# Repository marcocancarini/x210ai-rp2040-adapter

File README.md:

# X210Ai RP2040 adapter (rev 2.2)

> ⚠️ **Progetto interrotto**: lo sviluppo di questa scheda adattatore è stato sospeso perché le
> modifiche fatte via patch al firmware dell'EC (IT5571) hanno reso superfluo l'RP2040 esterno.
> Il reverse engineering dell'EC e le relative patch sono nella repo pubblica
> **[marcocancarini/x210ai-ec](https://github.com/marcocancarini/x210ai-ec)**
> (firmware EC patchato in [`firmware/patched/`](https://github.com/marcocancarini/x210ai-ec/tree/main/firmware/patched),
> strumento di patch in [`tools/patch_keyboard.py`](https://github.com/marcocancarini/x210ai-ec/blob/main/tools/patch_keyboard.py)).

Controller USB con RP2040 per la tastiera del ThinkPad X210Ai (ISO italiana e JIS giapponese), su due schede:
**Board A** (RP2040, sotto il palmrest) e **Board B** (flessibile a scalino sul connettore tastiera BTB_R_CONN1),
collegate da un cavo eDP 40 pin. Dettagli in [`passaggio.md`](passaggio.md) e
[`doc/REPORT_rev2.2.md`](doc/REPORT_rev2.2.md).

## Render
Tutti i PNG in [`render/`](render/): viste 2D dei layer a 40 px/mm (`gen2/render.py`) e render 3D
(`kicad-cli pcb render`, 1600×900).

### Board A (28,9 × 16,4 mm)

| 3D top | 3D bottom |
|---|---|
|  |  |
|  |  |

### Board B (29,1 × 28,8 mm)

| 3D top | 3D bottom |
|---|---|
|  |  |
|  |  |

## Checklist

Aggiornata al 28/10/2026 (versione `v2.2.0-rc1`). "Fatto" = verificato sul progetto, non su una scheda costruita.

### Fatto

**Progetto**
- [x] Architettura a due schede + cavo eDP (rev 2.2)
- [x] Modello dati separato: `gen2/design_boardA.py`, `gen2/design_boardB.py`, `gen2/edp_pinout.py`; script di `gen2/` con `--board A|B`
- [x] Firmware (hektopuss `970379d`) invariato: GPIO della Board A coincidenti con `x210ai_pins.h`, `fw3/out/*.uf2` valido
- [x] Emulazione firmware: 14/14 prove, 94/94 tasti (`emu2/`); simulazioni SPICE dei MOSFET EC e del TrackPoint (`spice2/`)
- [x] Impronte: `JAE_AA01B-S040VA1_T61` (44/44 piazzole come il Gerber T61; variante `_GND41` con le linguette a pin 41), `JAE_AA01B-P040_MB_Plug_Bottom`, `IPEX_20455-040E_90deg`
- [x] Specifica del cavo: [`doc/CABLE_SPEC.md`](doc/CABLE_SPEC.md)
- [x] Ambiente locale (Linux): KiCad 10.0.7, `.venv/` con shapely/gerbonara/cairosvg, Freerouting 1.9.0 + Java 21, ngspice 47, arduino-cli + arduino-pico 6.3.0, `emu2/node_modules`

**Schede**
- [x] Board B a L rovesciata a sandwich (39,7 × 15,4 mm): scartata, sopra la spina della tastiera non c'è spazio (non entra nemmeno una moneta da 5 centesimi, 1,67 mm)
- [x] Board B **a scalino** (29,1 × 28,8 mm): gradino alto con la spina J2 su BTB_R_CONN1, J4 verso il palmrest e Q2/Q3/R13/R14 sotto; scalino flessibile di 1,5 mm; gradino basso sulla scheda madre con il ricettacolo J1 della tastiera a 25° in senso orario. Ingombri dalla cornice di misura fotografata (`gen2/gen_dima_scala.py`), quadrato bianco come zona vietata; dima `doc/x210ai_dima_boardB_scalino_1a1.pdf` provata il 28/10/2026, legenda di tutti i componenti `doc/x210ai_dima_boardB_scalino_legenda.pdf`
- [x] Board B: PCB flessibile **4 strati** (poliimmide ~0,25 mm, In1 GND, via 0,4/0,2; a 2 strati le 30 linee J1 → J4 non si sbrogliano), irrigidimenti su User.1 (FR4 0,2 sopra J2 e sotto J4, poliimmide 0,1 sotto J1), zona di piega senza via. Uscite di J1 (ruotato di 25°) pre-instradate fino al gradino alto, poi Freerouting: ERC = 0, DRC = 0, 0 non connessi, schema = PCB; DFM: rame-bordo 0,25, ponte di maschera 0,2
- [x] Board A compattata a 28,9 × 16,4 mm (era 40 × 25): J4 sotto U1, TrackPoint in due colonne, via +3V3 dedicato per U1.48/49; dima provata sulla scheda madre il 28/10/2026
- [x] Sbroglio Freerouting di entrambe le schede (`-mp 100`): ERC = 0, DRC = 0, 0 non connessi, schema = PCB (`out_boardA/`, `out_boardB/`)
- [x] Isolamento foro-rame 0,2 mm rispettato alzando l'isolamento nel DSN (0,13 mm sulla Board B, 0,10 sulla Board A)
- [x] Controllo DFM: via 0,4/0,2 (A) e 0,3/0,15 (B, anello 0,075), pista minima 0,1, rame-bordo 0,25, ponte di maschera 0,2, via tutte coperte
- [x] KiCad 10: simboli nella libreria di progetto `x210ai.kicad_sym` + `sym-lib-table`, MOSFET da `Transistor_FET`, campi BOM nascosti in serigrafia, testo speculare sul lato B

**Produzione**
- [x] Produttore: JLCPCB per entrambe le schede (Board A rigida 4 strati 0,8 mm; Board B flessibile 4 strati con irrigidimenti)
- [x] Gerber, forature, BOM e CPL (un lato / due lati) per le due schede (`produzione/boardA/`, `produzione/boardB/`); controllo Gerber superato
- [x] Ricettacolo eDP C5160883 a magazzino LCSC (28/10/2026)
- [x] Spessori: Board B gradino alto ~2,0 mm (con irrigidimento), J4 innestato ~2,9 mm, gradino basso con spina e flat della tastiera ~2,9 mm; Board A ~3,1 mm su 4,0
- [x] Documenti rev 2.2: [`doc/LEGGIMI.md`](doc/LEGGIMI.md), [`doc/FIRMWARE.md`](doc/FIRMWARE.md), [`doc/VERIFICA.md`](doc/VERIFICA.md), [`doc/REPORT_rev2.2.md`](doc/REPORT_rev2.2.md)
- [x] Pacchetto `x210ai_iso_adapter_kicad_rev2.2.zip` (`gen2/make_pkg.py`)

### Da fare

**In sospeso (29/10/2026)**
- [ ] Board B: il flessibile a 4 strati con irrigidimenti costa troppo; da cercare una soluzione più economica (il progetto a scalino resta come riferimento: dima, ingombri misurati e legenda in `doc/`)
- [ ] Cavo: in attesa della risposta di LCSC Custom Cables (mail inviata il 29/10/2026)

**Board C (rev 2.3, in prova — 02/11/2026)**: integrazione di Board A + Board B in una scheda unica
senza cavo eDP, che aggira il quadrato bianco (zona vietata, < 1 mm sopra): si innesta su BTB_R_CONN1,
passa sotto e a sinistra del quadrato e mette le componenti del RP2040 sopra il quadrato (lato opposto
al connettore). Dime 1:1 in `doc/`: `x210ai_dima_boardC_1a1.pdf` (v1), `x210ai_dima_boardC_v2_1a1.pdf` (v2, ruotata 90° antiorario), `x210ai_dima_boardC_v3_1a1.pdf` (v3 = v2 tagliata a x = 9 mm; 2134 mm²) · `x210ai_dima_boardC_v4_1a1.pdf` (v4 = v3 + invade lo slot SIM di 2,2 mm, parte bassa della U tagliata di 2 mm, lato sinistro allargato di 7 mm; 2545 mm²); generate da `gen2/gen_dima_giro.py` (`--rot90ccw`, `--v3`, `--v4`);
misure dalla foto con dima millimetrata in `riferimenti/misure/`.

**Board C integrata (02/11/2026)**: `gen2/design_boardC.py` (`--board C` in tutti gli script, uscite in
`out_boardC/`). Struttura della rev 2.0: **J1 sopra e J2 sotto allineati a (0,0)** su BTB_R_CONN1, stessa
netlist (Q2b/Q3 per Fn+PgUp verso l'EC, pin 19 diretto), firmware invariato. Contorno = forma v3.2 della dima
(`x210ai_dima_boardC_v3_2_1a1.pdf`); gruppo RP2040 + TrackPoint della Board A **sotto**, nel braccio
dall'altra parte del quadrato bianco (la scheda madre è coperta di Mylar); PCB 4 strati 0,4 mm.

**Prima di ordinare**
- [ ] Misurare col calibro la distanza tra le file della spina 2×22 del flat (oggi stimata 3,9 mm)
- [x] Cavo: tipo **1-N** (il cavo non si capovolge lungo il percorso), lunghezza **150 o 200 mm** (`doc/CABLE_SPEC.md`)
- [ ] Cavo: micro-coassiale I-PEX 20453 a 40 fili, nessun pin unito, barra di massa ai due capi. Preventivo chiesto a LCSC Custom Cables (`cable@lcsc.com`) per i tipi 1-N (progetto) e 1-1 (riserva), 150 o 200 mm, tratti piatti alle spine e fascio tondo nel mezzo, in opzione curva a 90°. Alternative: produttore su Alibaba (~11 $/pz) o I-PEX 81422-100B-02-D da DigiKey (200 mm). I cavi eDP generici per pannelli 4K non vanno bene
- [ ] Board B: confermare nel configuratore JLCPCB flex: 4 strati, spessore, componenti sui due lati, irrigidimenti (file User.1), via 0,4/0,2, piste 0,1 mm
- [ ] Board B: col Patafix, spazio sopra il gradino basso (ricettacolo + spina della tastiera, ~2,9 mm) e sopra J4 (~2,9 mm)

**Facoltativo**
- [ ] Rivedere in KiCad lo sbroglio automatico e ritoccarlo a mano dove serve; J4 della Board B resta a 0,45 mm dal flat arancione
- [ ] Serigrafia: testi 0,45-0,7 mm e linee 0,12 mm sotto i minimi consigliati (1,0 / 0,15 mm), possono risultare poco leggibili

**Costruzione e prova**
- [ ] Ordinare PCB, componenti e cavo
- [ ] Saldare a mano la Board B (spina JAE J2 sotto, non su LCSC); Kapton sulla scheda madre sotto il gradino basso
- [ ] Prova di continuità del cavo pin per pin (`doc/CABLE_SPEC.md`)
- [ ] Prove a scheda montata: matrice, TrackPoint, Fn+PgUp → ThinkLight, accensione, swap Fn/Ctrl, JIS, UF2

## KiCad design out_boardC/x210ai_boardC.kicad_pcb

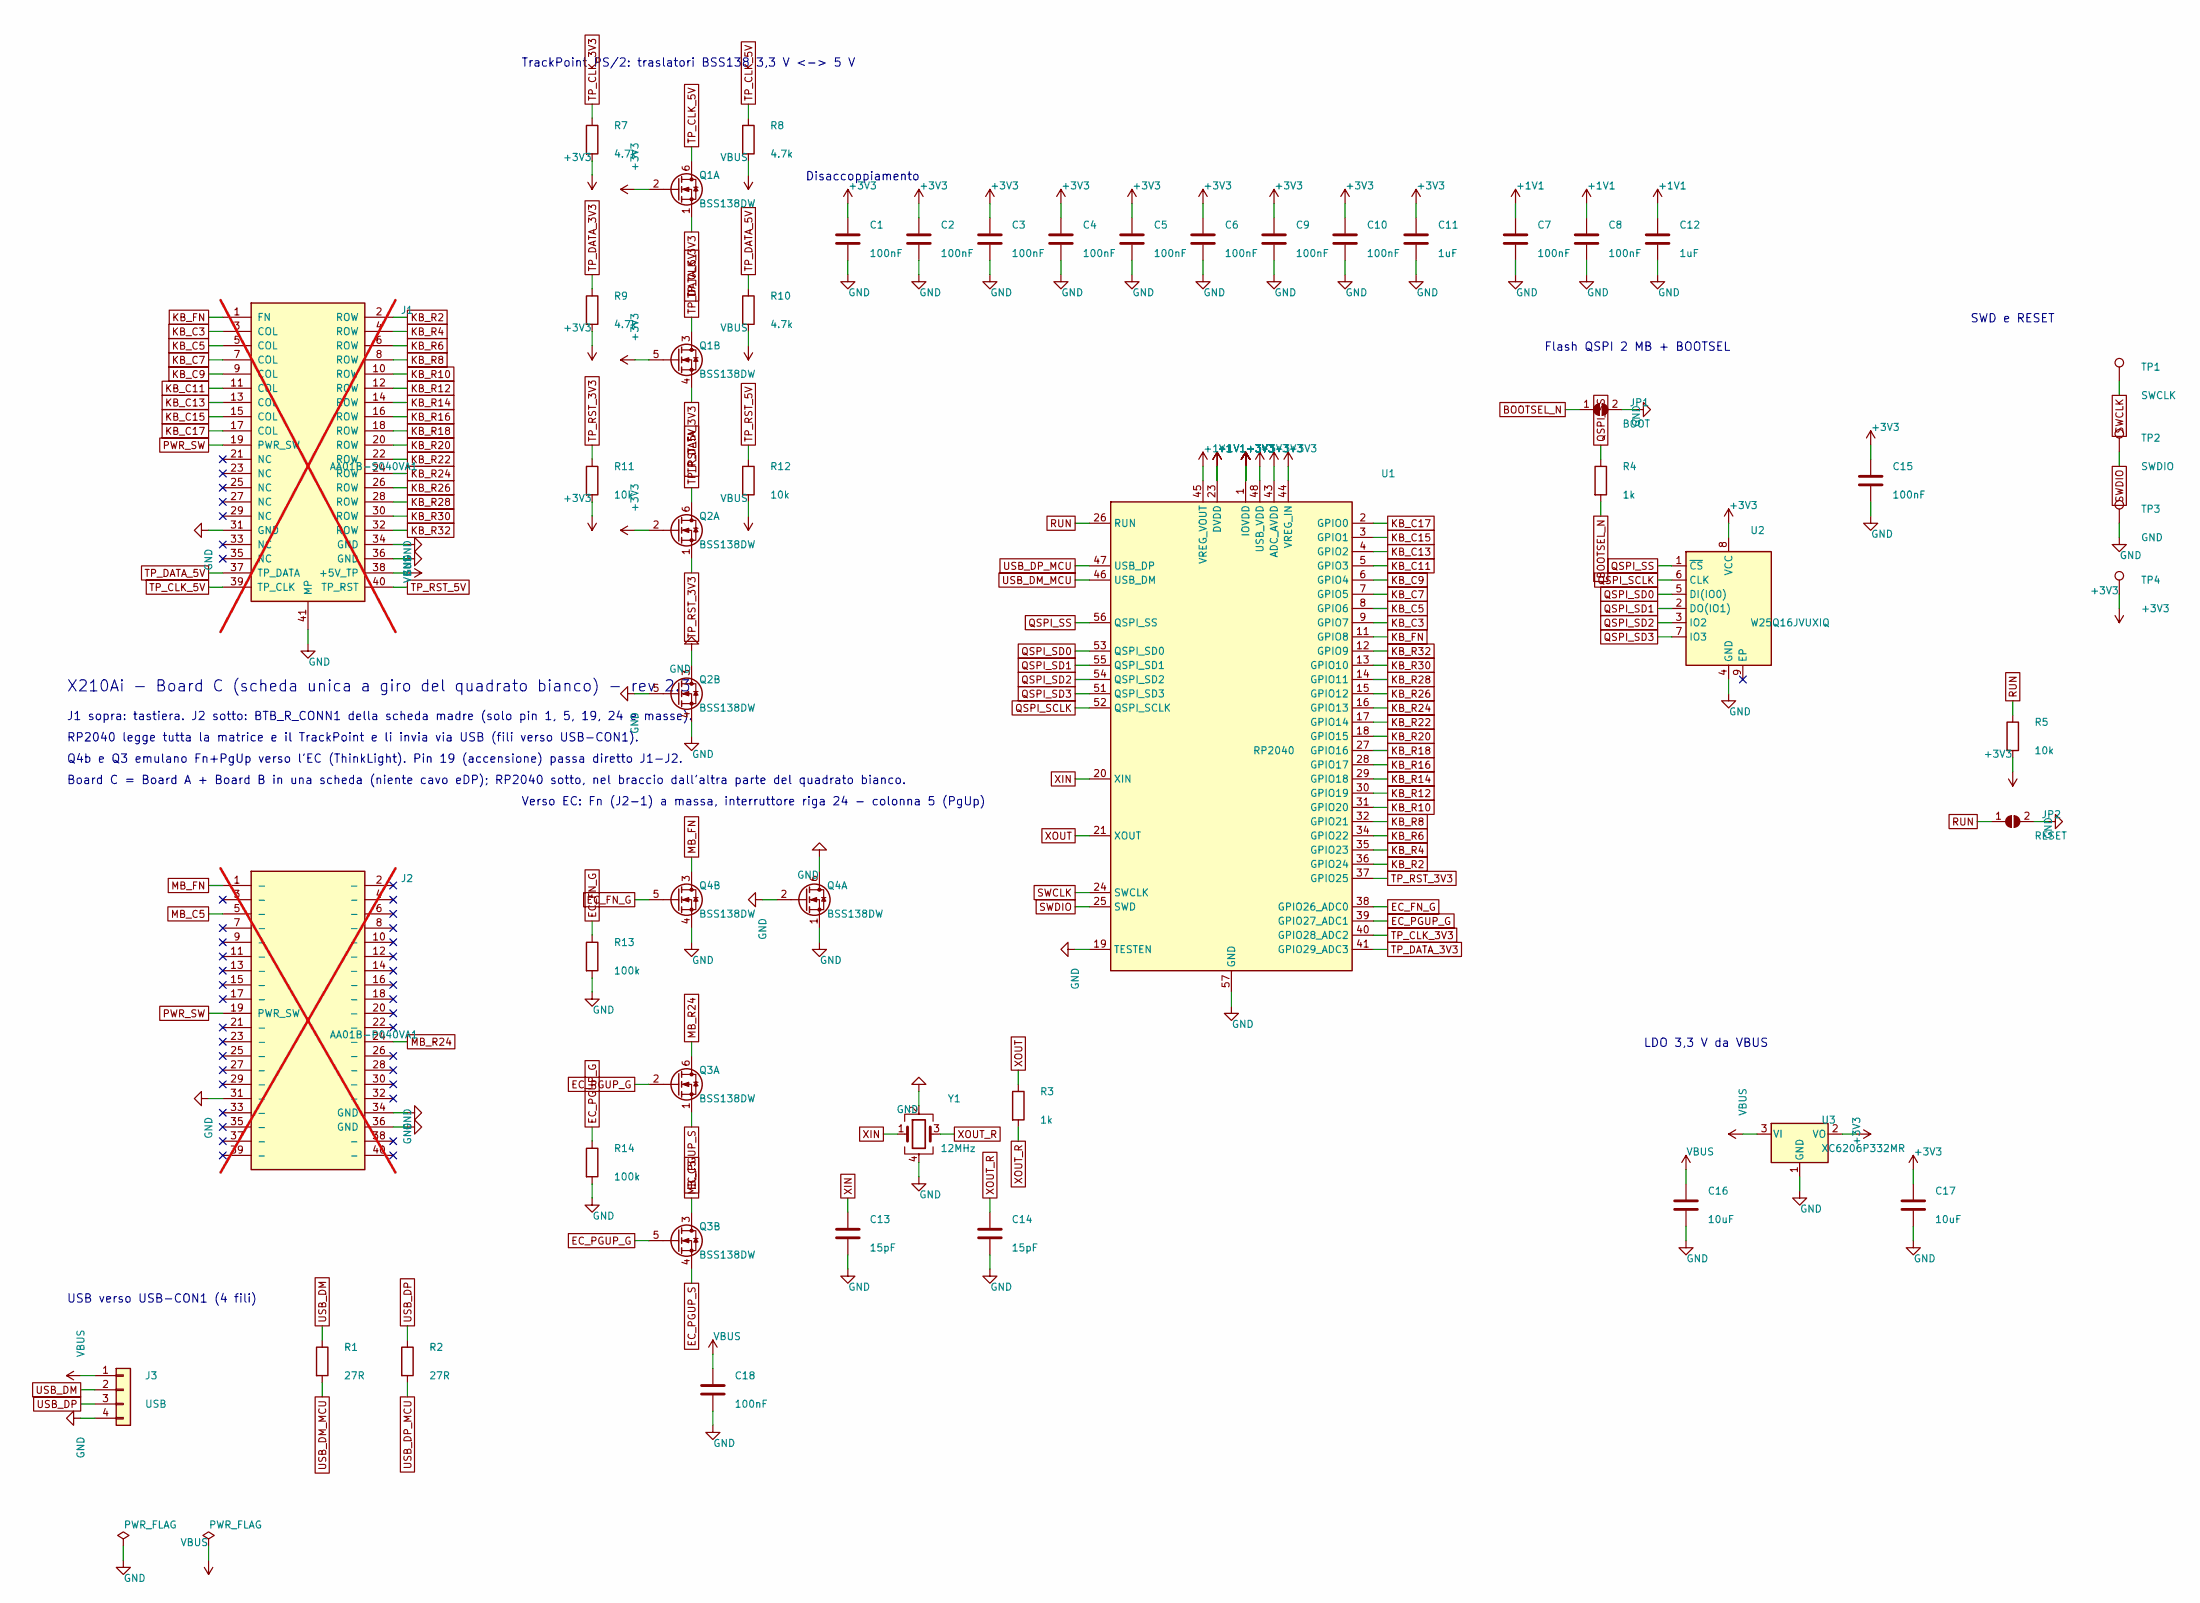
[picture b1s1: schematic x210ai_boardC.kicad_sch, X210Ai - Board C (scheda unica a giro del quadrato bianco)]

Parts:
C1, C2, C3, C4, C5, C6, C7, C8, C9, C10, C15, C18: 100nF; C_0402_1005Metric; MPN CL05B104KO5NNNC; LCSC C1525
C11, C12: 1uF; C_0402_1005Metric; MPN CL05A105KA5NQNC; LCSC C52923
C13, C14: 15pF; C_0402_1005Metric; MPN CL05C150JB5NNNC; LCSC C1548
C16, C17: 10uF; C_0402_1005Metric; MPN CL05A106MQ5NUNC; LCSC C15525
J1: AA01B-S040VA1; JAE_AA01B-S040VA1_KB_Receptacle; MPN AA01B-S040VA1-R3000; LCSC C2938571; not fitted
J2: AA01B-P040VA1; JAE_AA01B-P040_MB_Plug_Bottom; MPN AA01B-P040VA1-R3000; not fitted
J3: USB; Pads_1x04_P1.60mm_Wire_Edge
JP1: BOOT; SolderJumper-2_P1.3mm_Open_RoundedPad1.0x1.5mm
JP2: RESET; SolderJumper-2_P1.3mm_Open_RoundedPad1.0x1.5mm
Q1, Q2, Q3, Q4: BSS138DW; SOT-363_SC-70-6_Tight; MPN BSS138DW-7-F; LCSC C154900
R1, R2: 27R; R_0402_1005Metric; MPN 0402WGF270JTCE; LCSC C25100
R3, R4: 1k; R_0402_1005Metric; MPN 0402WGF1001TCE; LCSC C11702
R5, R11, R12: 10k; R_0402_1005Metric; MPN 0402WGF1002TCE; LCSC C25744
R7, R8, R9, R10: 4.7k; R_0402_1005Metric; MPN 0402WGF4701TCE; LCSC C25900
R13, R14: 100k; R_0402_1005Metric; MPN 0402WGF1003TCE; LCSC C25741
TP1: SWCLK; TP_Pad_1.0x1.0mm
TP2: SWDIO; TP_Pad_1.0x1.0mm
TP3: GND; TP_Pad_1.0x1.0mm
TP4: +3V3; TP_Pad_1.0x1.0mm
U1: RP2040; QFN-56-1EP_7x7mm_P0.4mm_EP3.2x3.2mm_ThermalVias; MPN RP2040; LCSC C2040
U2: W25Q16JVUXIQ; Winbond_USON-8-1EP_3x2mm_P0.5mm_EP0.2x1.6mm; MPN W25Q16JVUXIQ; LCSC C2843335
U3: XC6206P332MR; SOT-23-3; MPN XC6206P332MR-G; LCSC C5446
Y1: 12MHz; Crystal_SMD_3225-4Pin_3.2x2.5mm; MPN ABM8-272-T3; LCSC C20625731

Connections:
+1V1: C7.1, C8.1, C12.1, U1.23 (DVDD), U1.45 (VREG_VOUT), U1.50 (DVDD)
+3V3: C1.1, C2.1, C3.1, C4.1, C5.1, C6.1, C9.1, C10.1, C11.1, C15.1, C17.1, Q1.2 (G), Q1.5 (G), Q2.2 (G), R5.2, R7.2, R9.2, R11.2, TP4.1, U1.1 (IOVDD), U1.10 (IOVDD), U1.22 (IOVDD), U1.33 (IOVDD), U1.42 (IOVDD), U1.43 (ADC_AVDD), U1.44 (VREG_IN), U1.48 (USB_VDD), U1.49 (IOVDD), U2.8 (VCC), U3.2 (VO)
BOOTSEL_N: JP1.1 (A), R4.2
EC_FN_G: Q4.5 (G), R13.1, U1.38 (GPIO26_ADC0)
EC_PGUP_G: Q3.2 (G), Q3.5 (G), R14.1, U1.39 (GPIO27_ADC1)
EC_PGUP_S: Q3.1 (S), Q3.4 (S)
GND: C1.2, C2.2, C3.2, C4.2, C5.2, C6.2, C7.2, C8.2, C9.2, C10.2, C11.2, C12.2, C13.2, C14.2, C15.2, C16.2, C17.2, C18.2, J1.31 (GND), J1.34 (GND), J1.36 (GND), J1.41 (MP), J2.31 (-), J2.34 (GND), J2.36 (GND), J3.4, JP1.2 (B), JP2.2 (B), Q2.3 (D), Q2.4 (S), Q2.5 (G), Q4.1 (S), Q4.2 (G), Q4.4 (S), Q4.6 (D), R13.2, R14.2, TP3.1, U1.19 (TESTEN), U1.57 (GND), U2.4 (GND), U3.1 (GND), Y1.2, Y1.4
KB_C3: J1.3 (COL), U1.9 (GPIO7)
KB_C5: J1.5 (COL), U1.8 (GPIO6)
KB_C7: J1.7 (COL), U1.7 (GPIO5)
KB_C9: J1.9 (COL), U1.6 (GPIO4)
KB_C11: J1.11 (COL), U1.5 (GPIO3)
KB_C13: J1.13 (COL), U1.4 (GPIO2)
KB_C15: J1.15 (COL), U1.3 (GPIO1)
KB_C17: J1.17 (COL), U1.2 (GPIO0)
KB_FN: J1.1 (FN), U1.11 (GPIO8)
KB_R2: J1.2 (ROW), U1.36 (GPIO24)
KB_R4: J1.4 (ROW), U1.35 (GPIO23)
KB_R6: J1.6 (ROW), U1.34 (GPIO22)
KB_R8: J1.8 (ROW), U1.32 (GPIO21)
KB_R10: J1.10 (ROW), U1.31 (GPIO20)
KB_R12: J1.12 (ROW), U1.30 (GPIO19)
KB_R14: J1.14 (ROW), U1.29 (GPIO18)
KB_R16: J1.16 (ROW), U1.28 (GPIO17)
KB_R18: J1.18 (ROW), U1.27 (GPIO16)
KB_R20: J1.20 (ROW), U1.18 (GPIO15)
KB_R22: J1.22 (ROW), U1.17 (GPIO14)
KB_R24: J1.24 (ROW), U1.16 (GPIO13)
KB_R26: J1.26 (ROW), U1.15 (GPIO12)
KB_R28: J1.28 (ROW), U1.14 (GPIO11)
KB_R30: J1.30 (ROW), U1.13 (GPIO10)
KB_R32: J1.32 (ROW), U1.12 (GPIO9)
MB_C5: J2.5 (-), Q3.3 (D)
MB_FN: J2.1 (-), Q4.3 (D)
MB_R24: J2.24 (-), Q3.6 (D)
PWR_SW: J1.19 (PWR_SW), J2.19 (PWR_SW)
QSPI_SCLK: U1.52 (QSPI_SCLK), U2.6 (CLK)
QSPI_SD0: U1.53 (QSPI_SD0), U2.5 (DI(IO0))
QSPI_SD1: U1.55 (QSPI_SD1), U2.2 (DO(IO1))
QSPI_SD2: U1.54 (QSPI_SD2), U2.3 (IO2)
QSPI_SD3: U1.51 (QSPI_SD3), U2.7 (IO3)
QSPI_SS: R4.1, U1.56 (QSPI_SS), U2.1 (~CS)
RUN: JP2.1 (A), R5.1, U1.26 (RUN)
SWCLK: TP1.1, U1.24 (SWCLK)
SWDIO: TP2.1, U1.25 (SWD)
TP_CLK_3V3: Q1.1 (S), R7.1, U1.40 (GPIO28_ADC2)
TP_CLK_5V: J1.39 (TP_CLK), Q1.6 (D), R8.1
TP_DATA_3V3: Q1.4 (S), R9.1, U1.41 (GPIO29_ADC3)
TP_DATA_5V: J1.37 (TP_DATA), Q1.3 (D), R10.1
TP_RST_3V3: Q2.1 (S), R11.1, U1.37 (GPIO25)
TP_RST_5V: J1.40 (TP_RST), Q2.6 (D), R12.1
USB_DM: J3.2, R1.1
USB_DM_MCU: R1.2, U1.46 (USB_DM)
USB_DP: J3.3, R2.1
USB_DP_MCU: R2.2, U1.47 (USB_DP)
VBUS: C16.1, C18.1, J1.38 (+5V_TP), J3.1, R8.2, R10.2, R12.2, U3.3 (VI)
XIN: C13.1, U1.20 (XIN), Y1.1
XOUT: R3.1, U1.21 (XOUT)
XOUT_R: C14.1, R3.2, Y1.3

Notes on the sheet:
X210Ai - Board C (scheda unica a giro del quadrato bianco) - rev 2.3
J1 sopra: tastiera. J2 sotto: BTB_R_CONN1 della scheda madre (solo pin 1, 5, 19, 24 e masse).
RP2040 legge tutta la matrice e il TrackPoint e li invia via USB (fili verso USB-CON1).
TrackPoint PS/2: traslatori BSS138 3,3 V <-> 5 V
Verso EC: Fn (J2-1) a massa, interruttore riga 24 - colonna 5 (PgUp)
Disaccoppiamento
Flash QSPI 2 MB + BOOTSEL
LDO 3,3 V da VBUS
USB verso USB-CON1 (4 fili)
SWD e RESET
Board C = Board A + Board B in una scheda (niente cavo eDP); RP2040 sotto, nel braccio dall'altra parte del quadrato bianco.
Q4b e Q3 emulano Fn+PgUp verso l'EC (ThinkLight). Pin 19 (accensione) passa diretto J1-J2.

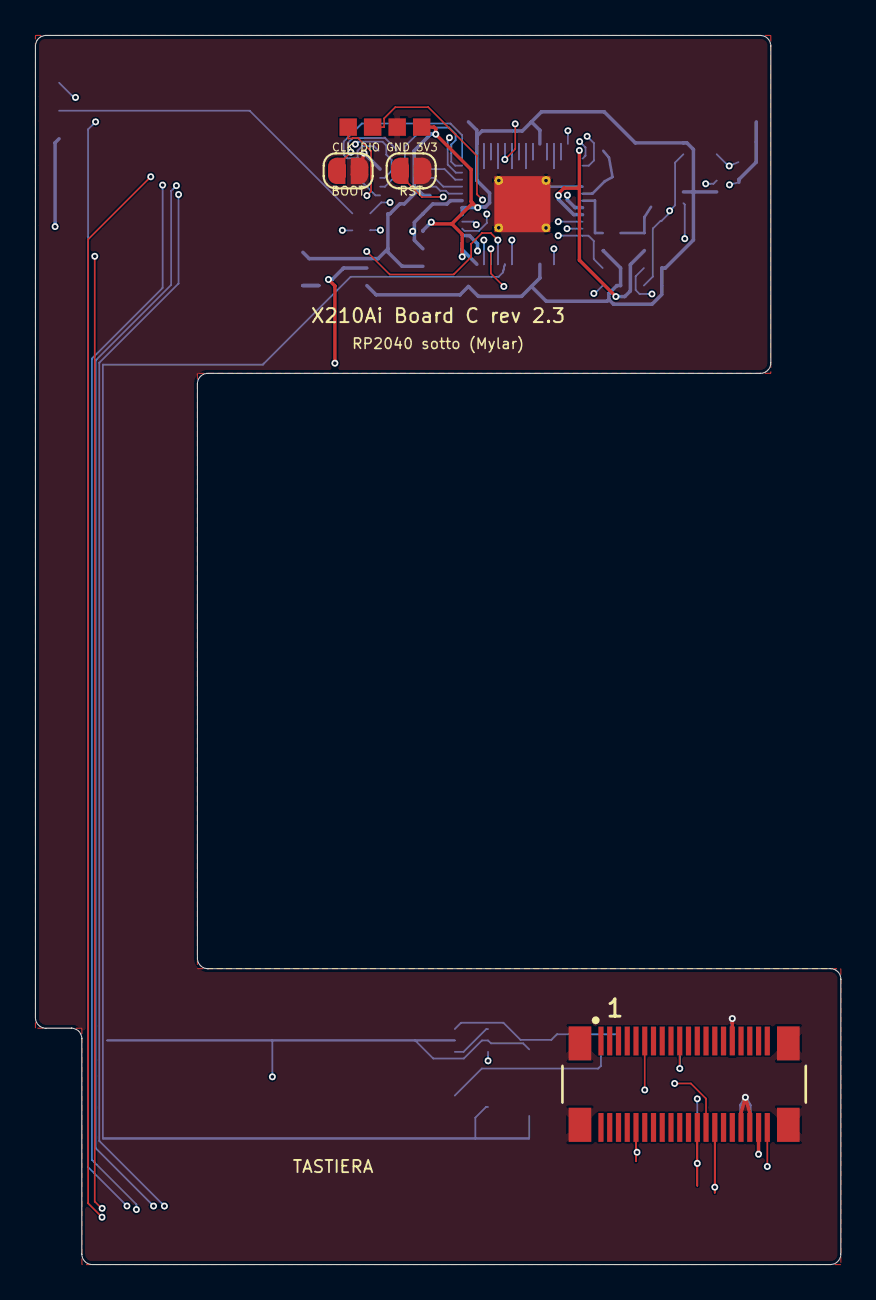
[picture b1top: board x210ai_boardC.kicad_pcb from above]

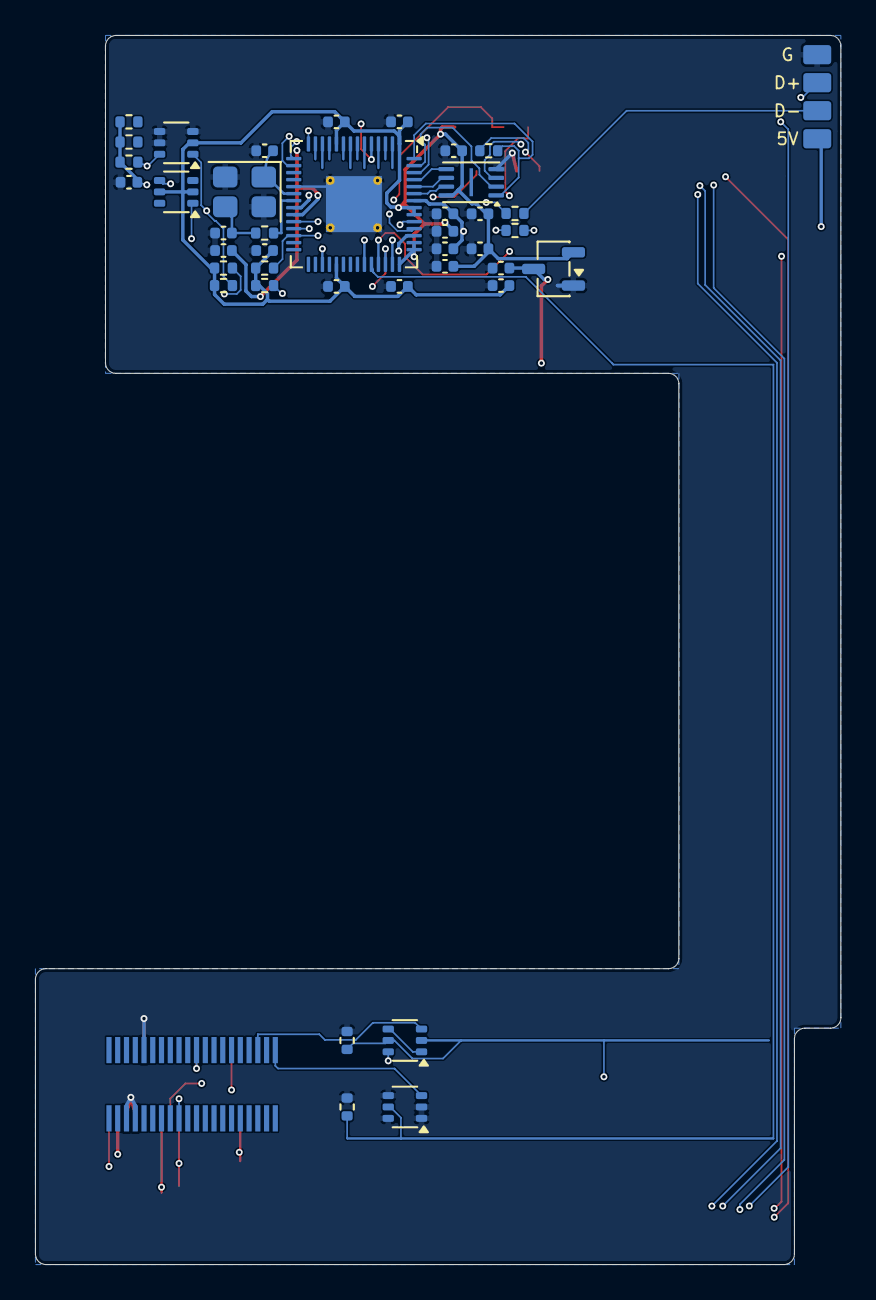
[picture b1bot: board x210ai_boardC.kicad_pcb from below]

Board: 4 copper layers, 46.0 x 70.2 mm, 48 parts (41 on the bottom side), 59 nets.

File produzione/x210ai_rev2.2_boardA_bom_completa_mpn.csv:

Designator,Value,Manufacturer,MPN,LCSC,Footprint,Side,Assembly,Note
C1,100nF,Samsung,CL05B104KO5NNNC,C1525,C_0402_1005Metric,Bottom,si,disaccoppiamento IOVDD/USB_VDD/ADC
C2,100nF,Samsung,CL05B104KO5NNNC,C1525,C_0402_1005Metric,Bottom,si,disaccoppiamento IOVDD/USB_VDD/ADC
C3,100nF,Samsung,CL05B104KO5NNNC,C1525,C_0402_1005Metric,Bottom,si,disaccoppiamento IOVDD/USB_VDD/ADC
C4,100nF,Samsung,CL05B104KO5NNNC,C1525,C_0402_1005Metric,Bottom,si,disaccoppiamento IOVDD/USB_VDD/ADC
C5,100nF,Samsung,CL05B104KO5NNNC,C1525,C_0402_1005Metric,Bottom,si,disaccoppiamento IOVDD/USB_VDD/ADC
C6,100nF,Samsung,CL05B104KO5NNNC,C1525,C_0402_1005Metric,Bottom,si,disaccoppiamento IOVDD/USB_VDD/ADC
C7,100nF,Samsung,CL05B104KO5NNNC,C1525,C_0402_1005Metric,Bottom,si,disaccoppiamento DVDD
C8,100nF,Samsung,CL05B104KO5NNNC,C1525,C_0402_1005Metric,Bottom,si,disaccoppiamento DVDD
C9,100nF,Samsung,CL05B104KO5NNNC,C1525,C_0402_1005Metric,Bottom,si,disaccoppiamento IOVDD/USB_VDD/ADC
C10,100nF,Samsung,CL05B104KO5NNNC,C1525,C_0402_1005Metric,Bottom,si,disaccoppiamento IOVDD/USB_VDD/ADC
C11,1uF,Samsung,CL05A105KA5NQNC,C52923,C_0402_1005Metric,Bottom,si,VREG_VIN
C12,1uF,Samsung,CL05A105KA5NQNC,C52923,C_0402_1005Metric,Bottom,si,VREG_VOUT
C13,15pF,Samsung,CL05C150JB5NNNC,C1548,C_0402_1005Metric,Bottom,si,carico quarzo
C14,15pF,Samsung,CL05C150JB5NNNC,C1548,C_0402_1005Metric,Bottom,si,carico quarzo
C15,100nF,Samsung,CL05B104KO5NNNC,C1525,C_0402_1005Metric,Bottom,si,disaccoppiamento flash
C16,10uF,Samsung,CL05A106MQ5NUNC,C15525,C_0402_1005Metric,Bottom,si,ingresso regolatore
C17,10uF,Samsung,CL05A106MQ5NUNC,C15525,C_0402_1005Metric,Bottom,si,uscita regolatore
C18,100nF,Samsung,CL05B104KO5NNNC,C1525,C_0402_1005Metric,Bottom,si,alimentazione TrackPoint
JP1,BOOT,,,,SolderJumper-2_P1.3mm_Open_RoundedPad1.0x1.5mm,Top,no (solo rame),ponticello BOOTSEL
JP2,RESET,,,,SolderJumper-2_P1.3mm_Open_RoundedPad1.0x1.5mm,Top,no (solo rame),ponticello RESET
J3,USB,,,,Pads_1x04_P1.60mm_Wire_Edge,Bottom,no (solo rame),fili verso USB-CON1
J4,20455-040E-76,I-PEX,20455-040E-76,C5160883,IPEX_20455-040E_90deg,Top,si,ricettacolo eDP verso la Board B
Q1,BSS138DW,Diodes Inc.,BSS138DW-7-F,C154900,SOT-363_SC-70-6_Tight,Bottom,si,traslatori PS/2 clock (a) e data (b)
Q2,BSS138DW,Diodes Inc.,BSS138DW-7-F,C154900,SOT-363_SC-70-6_Tight,Bottom,si,"traslatore reset TrackPoint (a); meta' b non usata, a massa"
R1,27R,UNI-ROYAL,0402WGF270JTCE,C25100,R_0402_1005Metric,Bottom,si,serie USB D-
R2,27R,UNI-ROYAL,0402WGF270JTCE,C25100,R_0402_1005Metric,Bottom,si,serie USB D+
R3,1k,UNI-ROYAL,0402WGF1001TCE,C11702,R_0402_1005Metric,Bottom,si,serie quarzo
R4,1k,UNI-ROYAL,0402WGF1001TCE,C11702,R_0402_1005Metric,Bottom,si,BOOTSEL
R5,10k,UNI-ROYAL,0402WGF1002TCE,C25744,R_0402_1005Metric,Bottom,si,pull-up RUN
R7,4.7k,UNI-ROYAL,0402WGF4701TCE,C25900,R_0402_1005Metric,Bottom,si,"pull-up PS/2 clock lato 3,3 V"
R8,4.7k,UNI-ROYAL,0402WGF4701TCE,C25900,R_0402_1005Metric,Bottom,si,pull-up PS/2 clock lato 5 V
R9,4.7k,UNI-ROYAL,0402WGF4701TCE,C25900,R_0402_1005Metric,Bottom,si,"pull-up PS/2 data lato 3,3 V"
R10,4.7k,UNI-ROYAL,0402WGF4701TCE,C25900,R_0402_1005Metric,Bottom,si,pull-up PS/2 data lato 5 V
R11,10k,UNI-ROYAL,0402WGF1002TCE,C25744,R_0402_1005Metric,Bottom,si,"pull-up reset TrackPoint lato 3,3 V"
R12,10k,UNI-ROYAL,0402WGF1002TCE,C25744,R_0402_1005Metric,Bottom,si,pull-up reset TrackPoint lato 5 V
TP1,SWCLK,,,,TP_Pad_1.0x1.0mm,Top,no (solo rame),test point SWD
TP2,SWDIO,,,,TP_Pad_1.0x1.0mm,Top,no (solo rame),test point SWD
TP3,GND,,,,TP_Pad_1.0x1.0mm,Top,no (solo rame),test point
TP4,+3V3,,,,TP_Pad_1.0x1.0mm,Top,no (solo rame),test point
U1,RP2040,Raspberry Pi,RP2040,C2040,QFN-56-1EP_7x7mm_P0.4mm_EP3.2x3.2mm_ThermalVias,Bottom,si,microcontrollore
U2,W25Q16JVUXIQ,Winbond,W25Q16JVUXIQ,C2843335,Winbond_USON-8-1EP_3x2mm_P0.5mm_EP0.2x1.6mm,Bottom,si,flash 2 MB (pad 9 lasciato libero)
U3,XC6206P332MR,Torex,XC6206P332MR-G,C5446,SOT-23-3,Bottom,si,"LDO 3,3 V"
Y1,12MHz,Abracon,ABM8-272-T3,C20625731,Crystal_SMD_3225-4Pin_3.2x2.5mm,Bottom,si,quarzo 12 MHz

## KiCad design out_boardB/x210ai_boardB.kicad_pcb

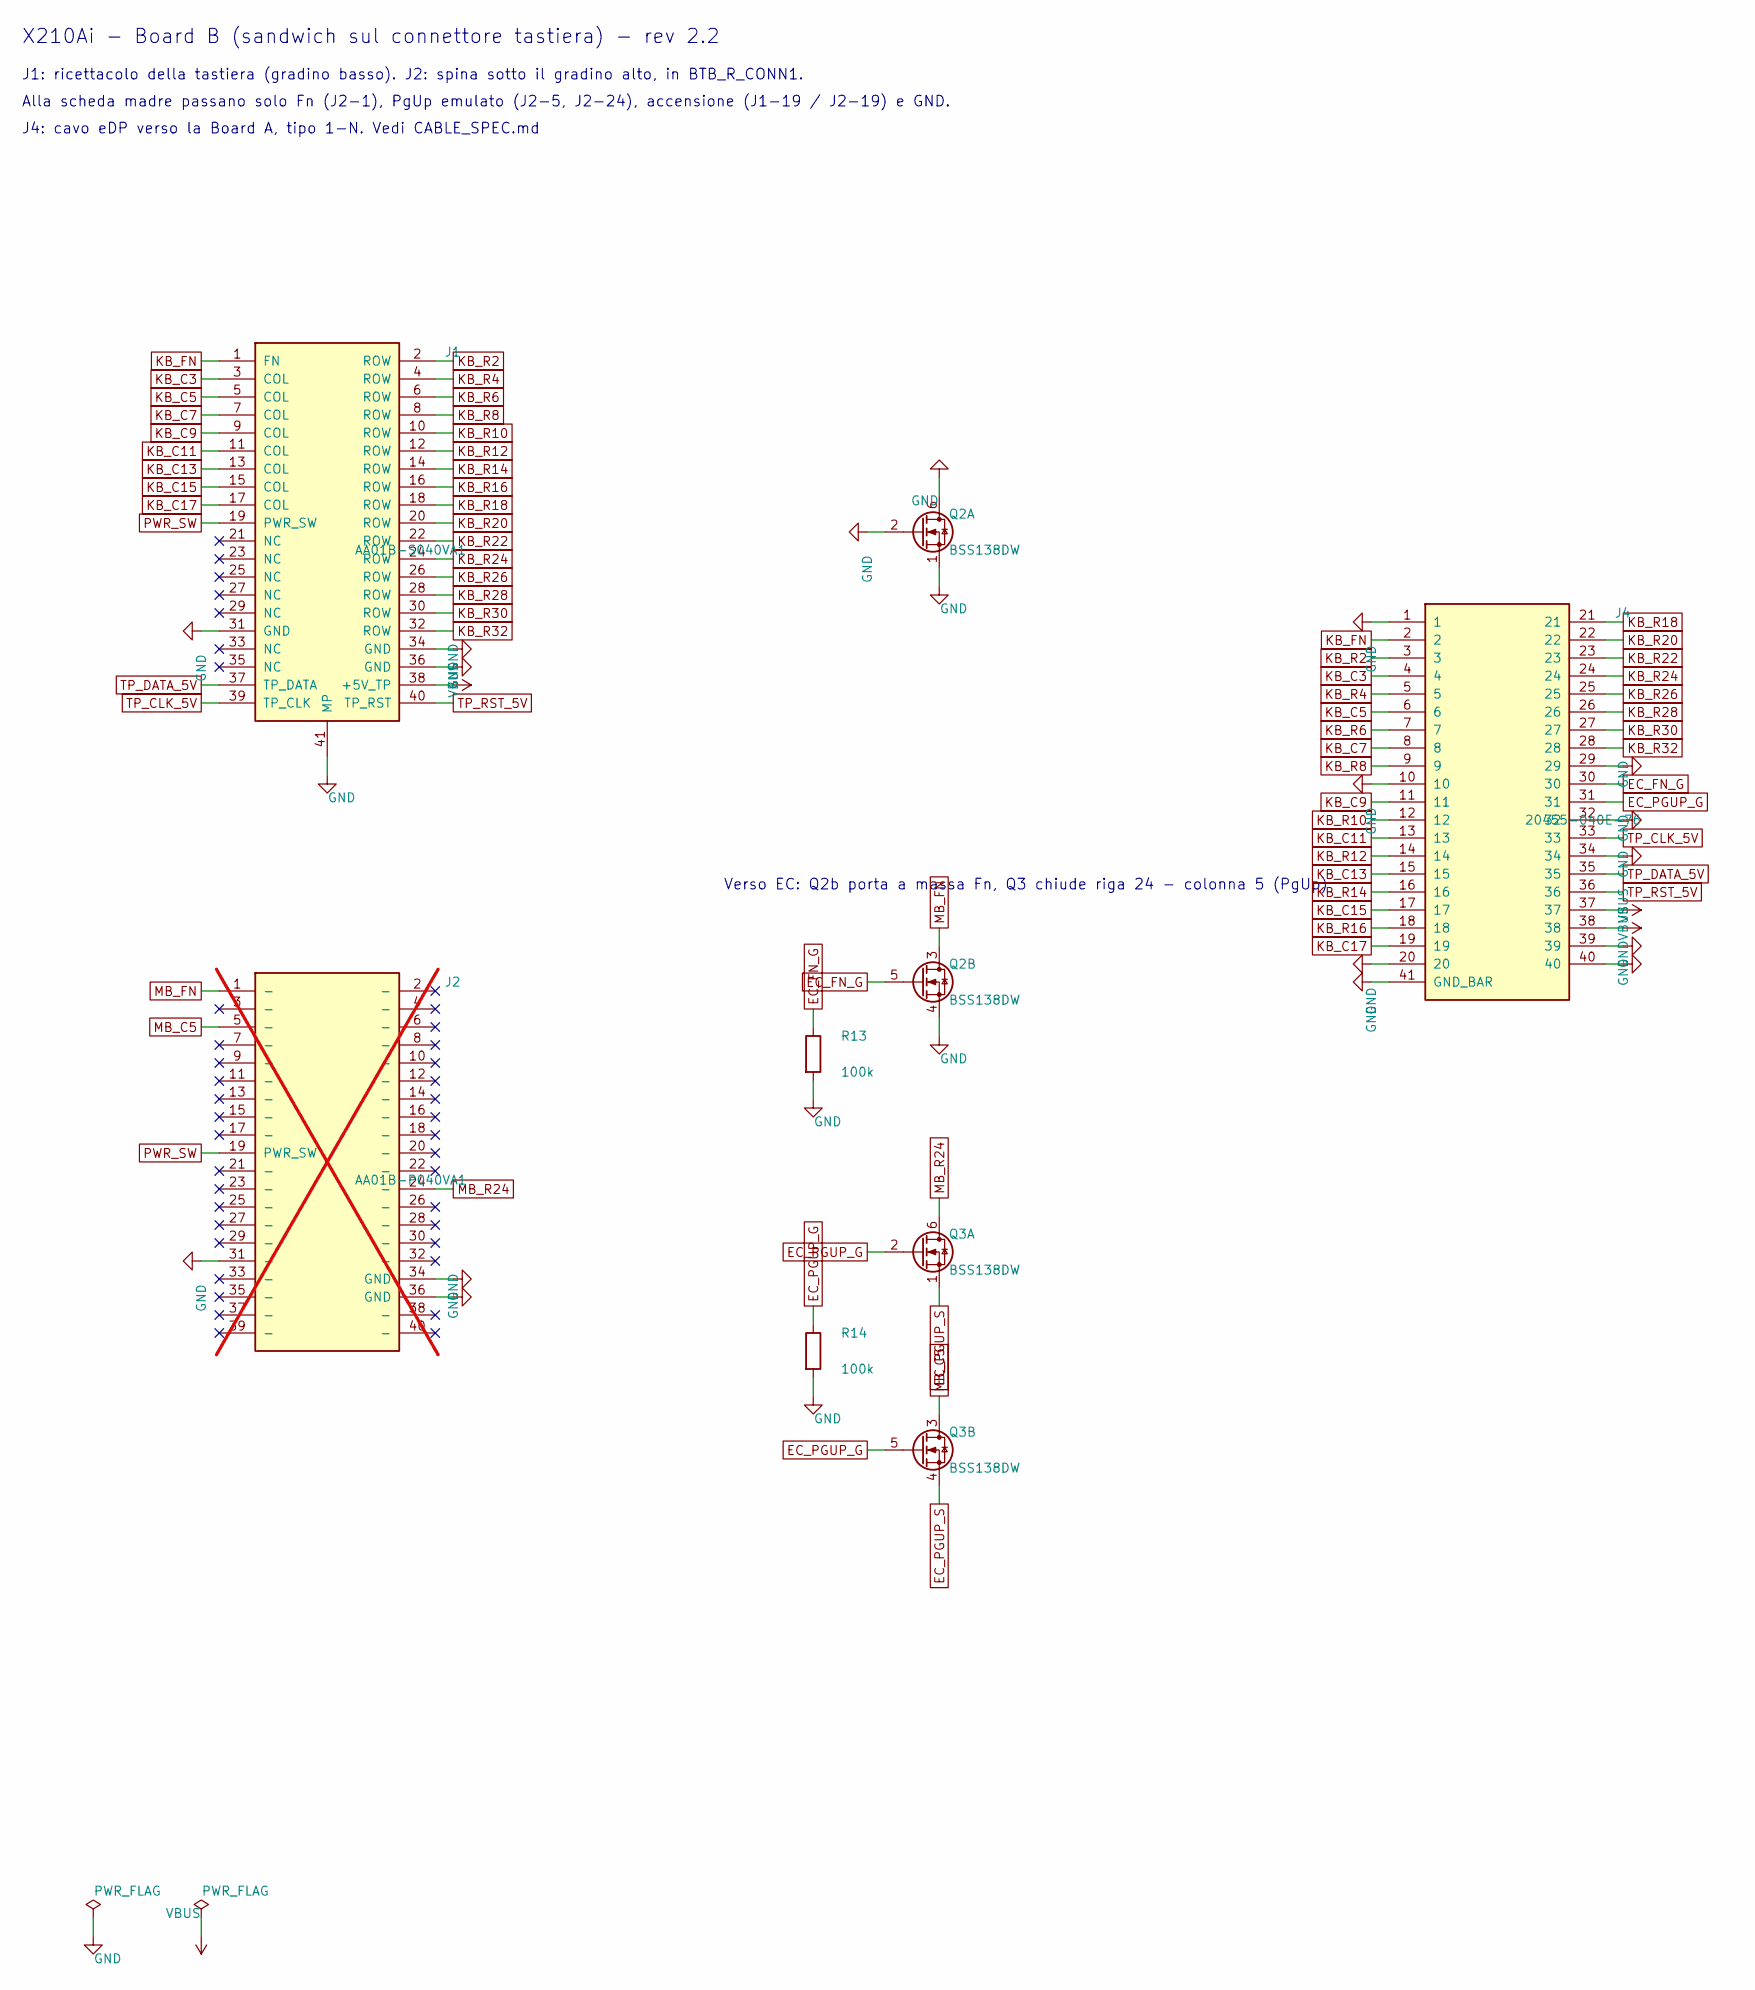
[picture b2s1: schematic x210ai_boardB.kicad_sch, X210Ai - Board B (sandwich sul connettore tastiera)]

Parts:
J1: AA01B-S040VA1; JAE_AA01B-S040VA1_T61_GND41; MPN AA01B-S040VA1-R3000; LCSC C2938571
J2: AA01B-P040VA1; JAE_AA01B-P040_MB_Plug_Bottom; MPN AA01B-P040VA1-R3000 (o spina 2x22 recup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; not fitted
J4: 20455-040E-76; IPEX_20455-040E_90deg; MPN 20455-040E-76; LCSC C5160883
Q2, Q3: BSS138DW; SOT-363_SC-70-6_Tight; MPN BSS138DW-7-F; LCSC C154900
R13, R14: 100k; R_0402_1005Metric; MPN 0402WGF1003TCE; LCSC C25741

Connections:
EC_FN_G: J4.30, Q2.5 (G), R13.1
EC_PGUP_G: J4.31, Q3.2 (G), Q3.5 (G), R14.1
EC_PGUP_S: Q3.1 (S), Q3.4 (S)
GND: J1.31 (GND), J1.34 (GND), J1.36 (GND), J1.41 (MP), J2.31 (-), J2.34 (GND), J2.36 (GND), J4.1, J4.10, J4.20, J4.29, J4.32, J4.34, J4.39, J4.40, J4.41 (GND_BAR), Q2.1 (S), Q2.2 (G), Q2.4 (S), Q2.6 (D), R13.2, R14.2
KB_C3: J1.3 (COL), J4.4
KB_C5: J1.5 (COL), J4.6
KB_C7: J1.7 (COL), J4.8
KB_C9: J1.9 (COL), J4.11
KB_C11: J1.11 (COL), J4.13
KB_C13: J1.13 (COL), J4.15
KB_C15: J1.15 (COL), J4.17
KB_C17: J1.17 (COL), J4.19
KB_FN: J1.1 (FN), J4.2
KB_R2: J1.2 (ROW), J4.3
KB_R4: J1.4 (ROW), J4.5
KB_R6: J1.6 (ROW), J4.7
KB_R8: J1.8 (ROW), J4.9
KB_R10: J1.10 (ROW), J4.12
KB_R12: J1.12 (ROW), J4.14
KB_R14: J1.14 (ROW), J4.16
KB_R16: J1.16 (ROW), J4.18
KB_R18: J1.18 (ROW), J4.21
KB_R20: J1.20 (ROW), J4.22
KB_R22: J1.22 (ROW), J4.23
KB_R24: J1.24 (ROW), J4.24
KB_R26: J1.26 (ROW), J4.25
KB_R28: J1.28 (ROW), J4.26
KB_R30: J1.30 (ROW), J4.27
KB_R32: J1.32 (ROW), J4.28
MB_C5: J2.5 (-), Q3.3 (D)
MB_FN: J2.1 (-), Q2.3 (D)
MB_R24: J2.24 (-), Q3.6 (D)
PWR_SW: J1.19 (PWR_SW), J2.19 (PWR_SW)
TP_CLK_5V: J1.39 (TP_CLK), J4.33
TP_DATA_5V: J1.37 (TP_DATA), J4.35
TP_RST_5V: J1.40 (TP_RST), J4.36
VBUS: J1.38 (+5V_TP), J4.37, J4.38

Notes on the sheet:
X210Ai - Board B (sandwich sul connettore tastiera) - rev 2.2
J1: ricettacolo della tastiera (gradino basso). J2: spina sotto il gradino alto, in BTB_R_CONN1.
Alla scheda madre passano solo Fn (J2-1), PgUp emulato (J2-5, J2-24), accensione (J1-19 / J2-19) e GND.
J4: cavo eDP verso la Board A, tipo 1-N. Vedi CABLE_SPEC.md
Verso EC: Q2b porta a massa Fn, Q3 chiude riga 24 - colonna 5 (PgUp)

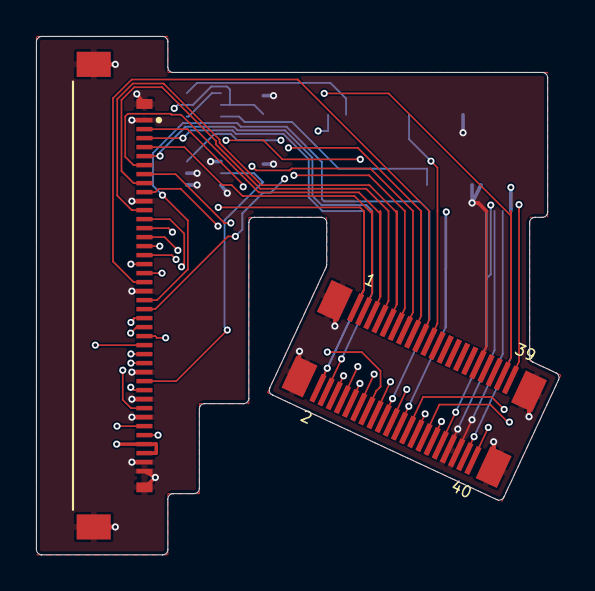
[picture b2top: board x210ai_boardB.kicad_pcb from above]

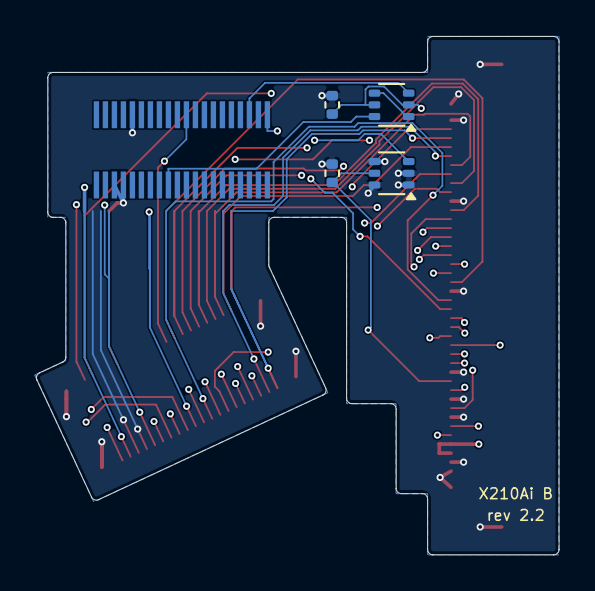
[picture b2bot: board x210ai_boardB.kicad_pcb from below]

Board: 4 copper layers, 29.0 x 28.8 mm, 7 parts (5 on the bottom side), 37 nets.

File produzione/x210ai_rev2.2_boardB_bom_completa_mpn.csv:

Designator,Value,Manufacturer,MPN,LCSC,Footprint,Side,Assembly,Note
J1,AA01B-S040VA1,JAE,AA01B-S040VA1-R3000,C2938571,JAE_AA01_sandwich,Top,si,ricettacolo tastiera (sopra) + spina verso BTB_R_CONN1 (sotto)
J1,AA01B-P040VA1,JAE,AA01B-P040VA1-R3000 (o spina 2x22 recuperata da un flat),,JAE_AA01_sandwich,Bottom,"DNP - saldare a mano, non su LCSC",ricettacolo tastiera (sopra) + spina verso BTB_R_CONN1 (sotto)
J4,20455-040E-76,I-PEX,20455-040E-76,C5160883,IPEX_20455-040E_90deg,Top,si,ricettacolo eDP verso la Board A (cavo 1-N)
Q2,BSS138DW,Diodes Inc.,BSS138DW-7-F,C154900,SOT-363_SC-70-6_Tight,Bottom,si,meta' a non usata (a massa); b: Fn verso EC
Q3,BSS138DW,Diodes Inc.,BSS138DW-7-F,C154900,SOT-363_SC-70-6_Tight,Bottom,si,interruttore bidirezionale riga24-colonna5 (PgUp) verso EC
R13,100k,UNI-ROYAL,0402WGF1003TCE,C25741,R_0402_1005Metric,Bottom,si,pull-down gate Fn->EC
R14,100k,UNI-ROYAL,0402WGF1003TCE,C25741,R_0402_1005Metric,Bottom,si,pull-down gate PgUp->EC

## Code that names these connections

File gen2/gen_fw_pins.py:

# -*- coding: utf-8 -*-
"""Genera x210ai_pins.h dal modello dati: python gen_fw_pins.py [--board A] <sketch_dir>
(la Board A ha gli stessi GPIO della rev 2.0: cambia solo il commento in testa)"""
import os
import sys

sys.path.insert(0, os.path.dirname(os.path.abspath(__file__)))
import boards  # noqa: E402

D = boards.load()
assert hasattr(D, "SIGNAL_GPIO"), "il firmware gira sulla Board A: usa --board A"

out = os.path.join(sys.argv[1], "x210ai_pins.h")
G = D.SIGNAL_GPIO
txt = f"""// x210ai_pins.h - generato da gen2/gen_fw_pins.py (scheda-ponte X210Ai rev {D.REV}, {D.DATE})
// Non modificare a mano: i GPIO seguono il PCB.
#pragma once

// righe della matrice nell'ordine del firmware (pin connettore tastiera {D.FW_ROW_PINS})
#define X210_ROW_IO {{ {", ".join(map(str, D.ROW_IO))} }}
// colonne (pin connettore {D.FW_COL_PINS})
#define X210_COL_IO {{ {", ".join(map(str, D.COL_IO))} }}

#define X210_FN_PIN        {G["KB_FN"]}   // Fn, pin 1 del connettore (attivo basso)
#define X210_TP_DATA_PIN   {G["TP_DATA_3V3"]}  // PS/2 data TrackPoint (via BSS138)
#define X210_TP_CLOCK_PIN  {G["TP_CLK_3V3"]}  // PS/2 clock TrackPoint (via BSS138)
#define X210_TP_RESET_PIN  {G["TP_RST_3V3"]}  // reset TrackPoint, attivo alto (via BSS138)
#define X210_EC_FN_PIN     {G["EC_FN_G"]}  // gate Q2b: porta a massa il Fn della scheda madre
#define X210_EC_PGUP_PIN   {G["EC_PGUP_G"]}  // gate Q3: chiude riga 24 - colonna 5 (PgUp) verso l'EC
"""
open(out, "w").write(txt)
print(out)
